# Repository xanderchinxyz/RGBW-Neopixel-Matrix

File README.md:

# RGBW Neopixel Matrix

All of the code and PCB files for my RGBW Neopixel Matrix

YouTube video Part 1: https://youtu.be/KatHkq3PDNg

YouTube video Part 2: https://youtu.be/1C1XGq-2Q_g

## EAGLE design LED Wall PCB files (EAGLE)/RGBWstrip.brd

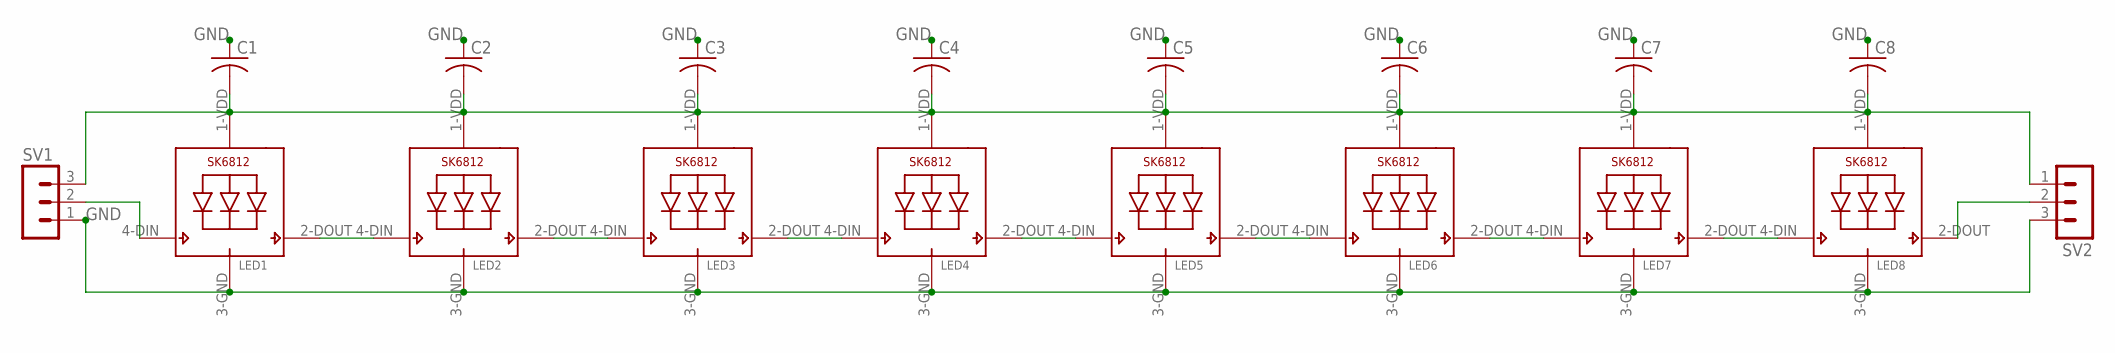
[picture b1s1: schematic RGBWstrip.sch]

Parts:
C1, C2, C3, C4, C5, C6, C7, C8: C-USC0805; C0805
LED1, LED2, LED3, LED4, LED5, LED6, LED7, LED8: SK6812_5050W; LED5050_W
SV1, SV2: MA03-1

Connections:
GND: C1.1, C2.1, C3.1, C4.1, C5.1, C6.1, C7.1, C8.1, LED1.3-GND (GND), LED2.3-GND (GND), LED3.3-GND (GND), LED4.3-GND (GND), LED5.3-GND (GND), LED6.3-GND (GND), LED7.3-GND (GND), LED8.3-GND (GND), SV1.1, SV2.3
unnamed: LED1.4-DIN (DI), SV1.2
unnamed: C1.2, C2.2, C3.2, C4.2, C5.2, C6.2, C7.2, C8.2, LED1.1-VDD (VDD), LED2.1-VDD (VDD), LED3.1-VDD (VDD), LED4.1-VDD (VDD), LED5.1-VDD (VDD), LED6.1-VDD (VDD), LED7.1-VDD (VDD), LED8.1-VDD (VDD), SV1.3, SV2.1
unnamed: LED8.2-DOUT (DO), SV2.2
unnamed: LED1.2-DOUT (DO), LED2.4-DIN (DI)
unnamed: LED2.2-DOUT (DO), LED3.4-DIN (DI)
unnamed: LED3.2-DOUT (DO), LED4.4-DIN (DI)
unnamed: LED4.2-DOUT (DO), LED5.4-DIN (DI)
unnamed: LED5.2-DOUT (DO), LED6.4-DIN (DI)
unnamed: LED6.2-DOUT (DO), LED7.4-DIN (DI)
unnamed: LED7.2-DOUT (DO), LED8.4-DIN (DI)

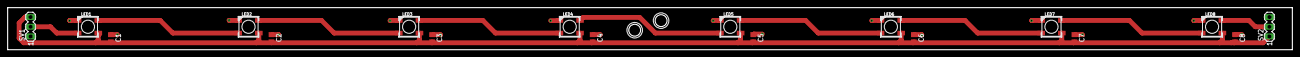
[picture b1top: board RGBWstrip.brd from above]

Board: 2 copper layers, 336.0 x 11.0 mm, 20 parts (0 on the bottom side), 11 nets.

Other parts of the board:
U$2, U$3: MOUNTINGHOLE_3.2MM_PLATEDTHIN

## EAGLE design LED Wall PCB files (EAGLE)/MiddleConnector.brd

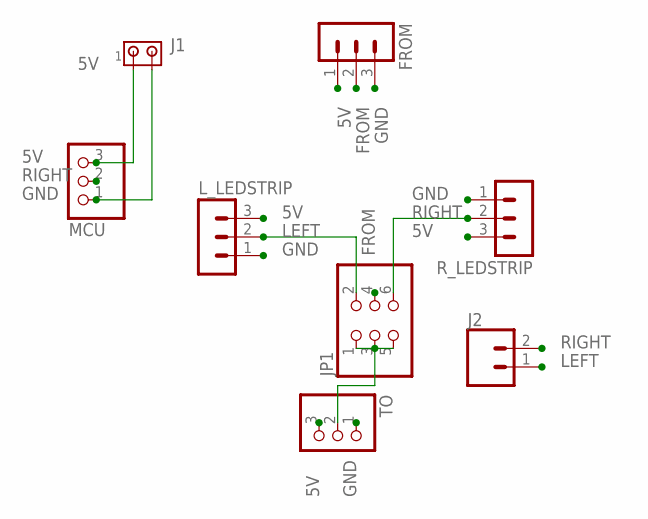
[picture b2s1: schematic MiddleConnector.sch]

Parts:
FROM: MA03-1
J1: MTA02-156; 1X2MTA
J2: CONN_02; 1X02
JP1: PINHD-2X3; 2X03
L_LEDSTRIP: MA03-1
MCU: PINHD-1X3/90; 1X03/90
R_LEDSTRIP: MA03-1
TO: PINHD-1X3/90; 1X03/90

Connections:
5V: FROM.1, J1.1, L_LEDSTRIP.3, MCU.3, R_LEDSTRIP.3, TO.3
FROM: FROM.2, JP1.4
GND: FROM.3, J1.2, L_LEDSTRIP.1, MCU.1, R_LEDSTRIP.1, TO.1
LEFT: J2.1, JP1.2, L_LEDSTRIP.2
unnamed: JP1.1, JP1.3, JP1.5, TO.2
RIGHT: J2.2, JP1.6, MCU.2, R_LEDSTRIP.2

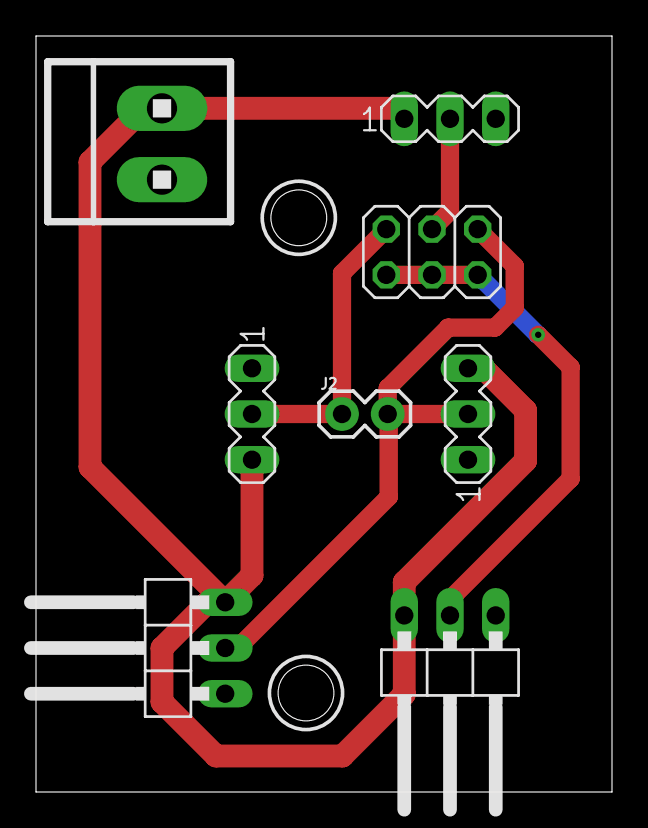
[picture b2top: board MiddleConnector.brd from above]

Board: 2 copper layers, 32.0 x 42.0 mm, 10 parts (0 on the bottom side), 6 nets.

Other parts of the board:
U$1, U$2: MOUNTINGHOLE_3.2MM_PLATEDTHIN

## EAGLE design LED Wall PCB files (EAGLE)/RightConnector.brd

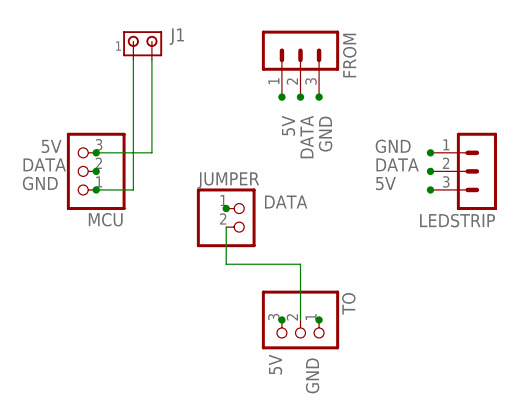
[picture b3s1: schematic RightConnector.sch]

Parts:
FROM: MA03-1
J1: MTA02-156; 1X2MTA
JUMPER: PINHD-1X2; 1X02
LEDSTRIP: MA03-1
MCU: PINHD-1X3/90; 1X03/90
TO: PINHD-1X3/90; 1X03/90

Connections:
5V: FROM.1, J1.2, LEDSTRIP.3, MCU.3, TO.3
DATA: FROM.2, JUMPER.1, LEDSTRIP.2, MCU.2
GND: FROM.3, J1.1, LEDSTRIP.1, MCU.1, TO.1
unnamed: JUMPER.2, TO.2

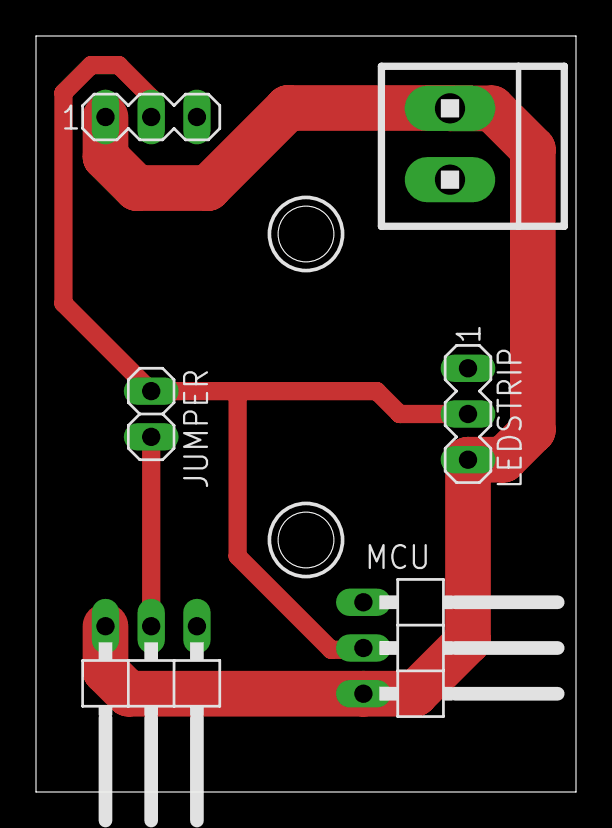
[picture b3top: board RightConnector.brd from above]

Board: 2 copper layers, 30.0 x 42.0 mm, 8 parts (0 on the bottom side), 4 nets.

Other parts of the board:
U$1, U$2: MOUNTINGHOLE_3.2MM_PLATEDTHIN

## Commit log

2022-05-03 Create hi
2022-08-24 changed folder names
2022-08-24 changed folder structures
2022-08-24 fwaerq
2022-08-26 added files

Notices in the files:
parts and their libraries:
SparkFun-Connectors: Licensing: Creative Commons ShareAlike 4.0 International - https://creativecommons.org/licenses/by-sa/4.0
